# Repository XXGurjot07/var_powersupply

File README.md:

# var_powersupply
# VARIABLE REGULATED DC BENCH POWER SUPPLY
 0. See Schematic.pdf for quick review.
 1. The Schematic, PCB Layout and Gerbers were generated in KiCAD.  
 2. All the values have been selected with due reference to the Datasheets only.  
 3. Output = 1.23 - 13.53 V @3A Max (for this Topology)  
 4. You can use other DC-DC Converted modules and change some component values and get yourself a custom Voltage and Current range.  
 5. For any queries/help with your design drop an email - 98762singh@gmail.com  
 6. Peace Out!

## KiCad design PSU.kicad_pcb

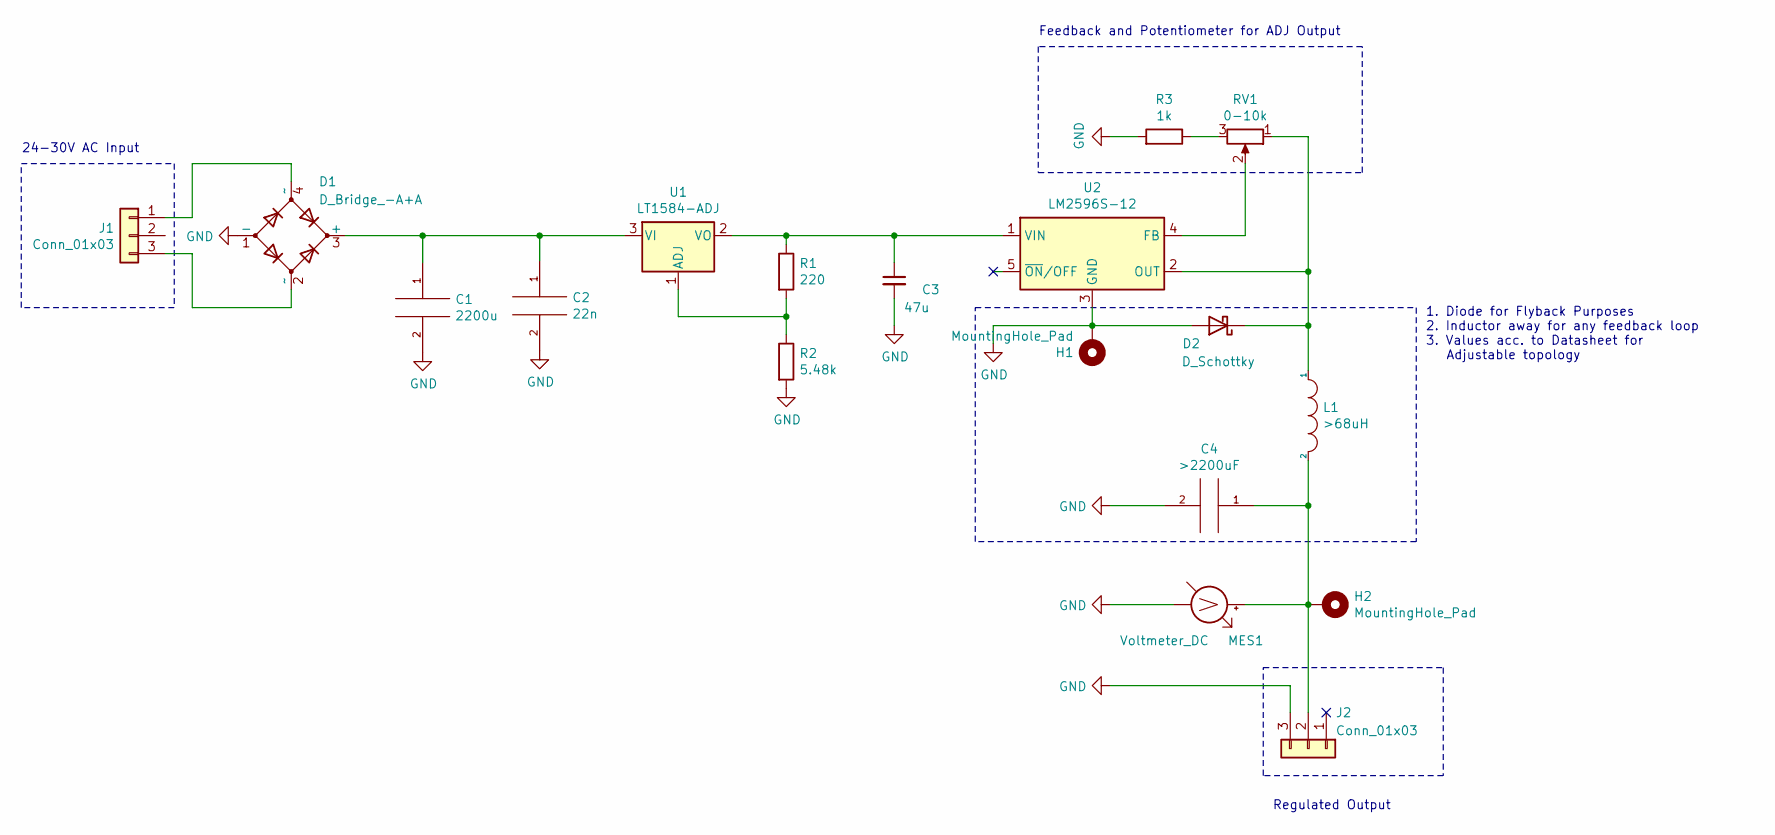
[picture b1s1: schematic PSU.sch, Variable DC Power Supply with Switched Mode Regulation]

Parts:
C1: 2200u; C_Radial_D18.0mm_H35.5mm_P7.50mm
C2: 22n; C_Rect_L7.0mm_W2.5mm_P5.00mm
C3: 47u; C_Radial_D4.0mm_H5.0mm_P1.50mm
C4: >2200uF; C_Radial_D18.0mm_H35.5mm_P7.50mm
D1: D_Bridge_-A+A; Diode_Bridge_Vishay_KBPC6
D2: D_Schottky; D_A-405_P7.62mm_Horizontal
H1, H2: MountingHole_Pad; MountingHole_2.5mm_Pad
J1, J2: Conn_01x03; TerminalBlock_Phoenix_MKDS-1,5-3_1x03_P5.00mm_Horizontal
L1: >68uH; L_Radial_D21.0mm_P14.61mm_Vishay_IHB-2
MES1: Voltmeter_DC; CA56-12SYKWA
R1: 220; R_Axial_DIN0204_L3.6mm_D1.6mm_P7.62mm_Horizontal
R2: 5.48k; R_Axial_DIN0204_L3.6mm_D1.6mm_P7.62mm_Horizontal
R3: 1k; R_Axial_DIN0204_L3.6mm_D1.6mm_P7.62mm_Horizontal
RV1: 0-10k; Potentiometer_Bourns_3299Y_Vertical
U1: LT1584-ADJ; TO-220-3_Vertical
U2: LM2596S-12; TO-263-5_TabPin3

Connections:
GND: C1.2, C2.2, C3.2, C4.2, D1.1 (-), D2.2 (A), H1.1, J2.3, MES1.1 (-), R2.2, R3.2, U2.3 (GND)
unnamed: C1.1, C2.1, D1.3 (+), U1.3 (VI)
unnamed: C3.1, R1.1, U1.2 (VO), U2.1 (VIN)
unnamed: C4.1, H2.1, J2.2, L1.2, MES1.2 (+)
unnamed: D1.2 (~~), J1.3
unnamed: D1.4 (~~), J1.1
unnamed: D2.1 (K), L1.1, RV1.1, U2.2 (OUT)
unnamed: R1.2, R2.1, U1.1 (ADJ)
unnamed: R3.1, RV1.3
unnamed: RV1.2, U2.4 (FB)

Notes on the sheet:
24-30V AC Input
Regulated Output
1. Diode for Flyback Purposes 2. Inductor away for any feedback loop 3. Values acc. to Datasheet for Adjustable topology
Feedback and Potentiometer for ADJ Output

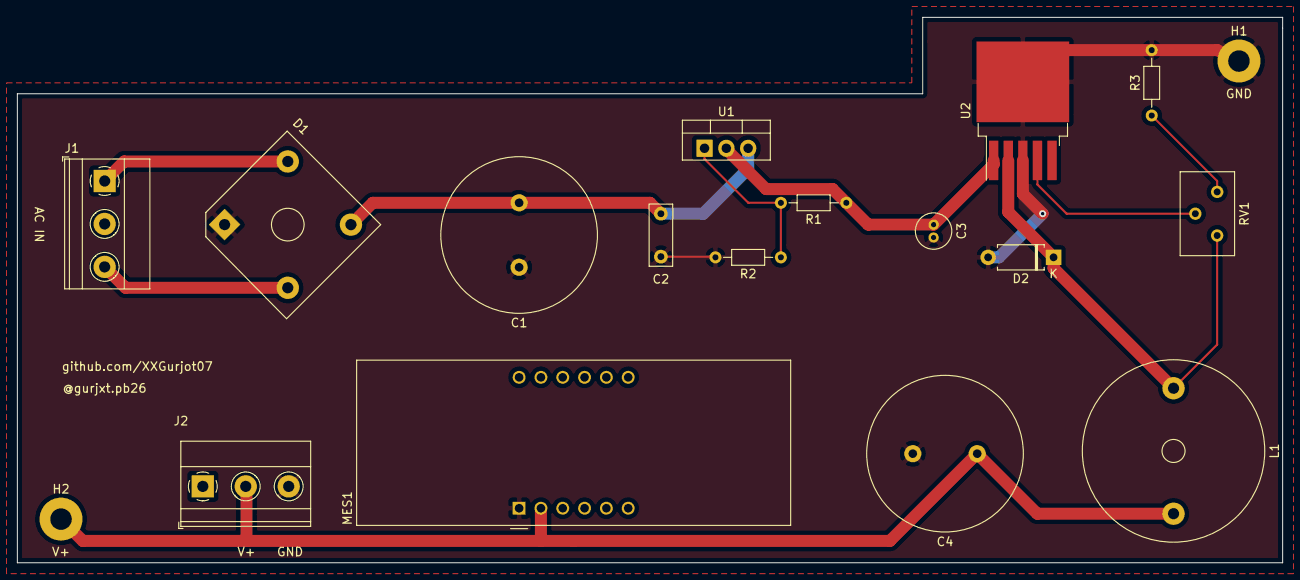
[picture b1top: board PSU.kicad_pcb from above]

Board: 2 copper layers, 147.3 x 63.5 mm, 18 parts (0 on the bottom side), 10 nets.

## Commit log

2021-12-29 Create gto
2021-12-30 Add files via upload
    3D Design Model with Components
